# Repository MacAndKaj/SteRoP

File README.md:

# SteRoP
A project with STM32L476 Discovery

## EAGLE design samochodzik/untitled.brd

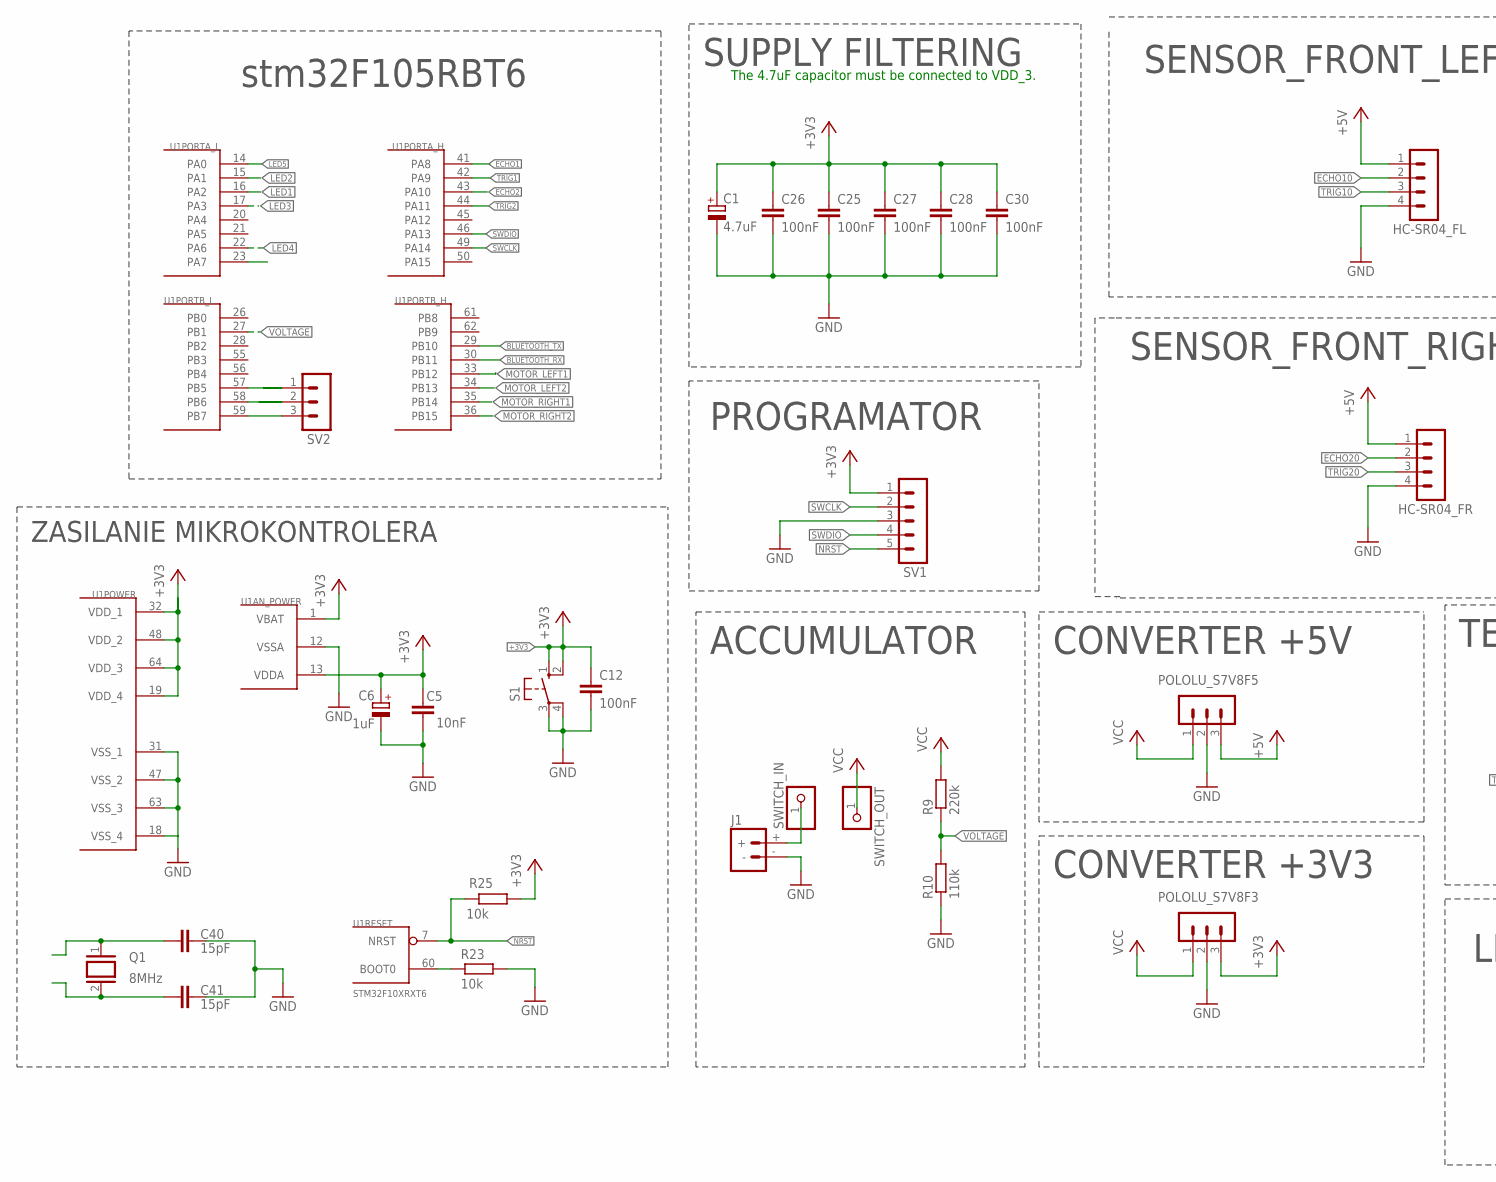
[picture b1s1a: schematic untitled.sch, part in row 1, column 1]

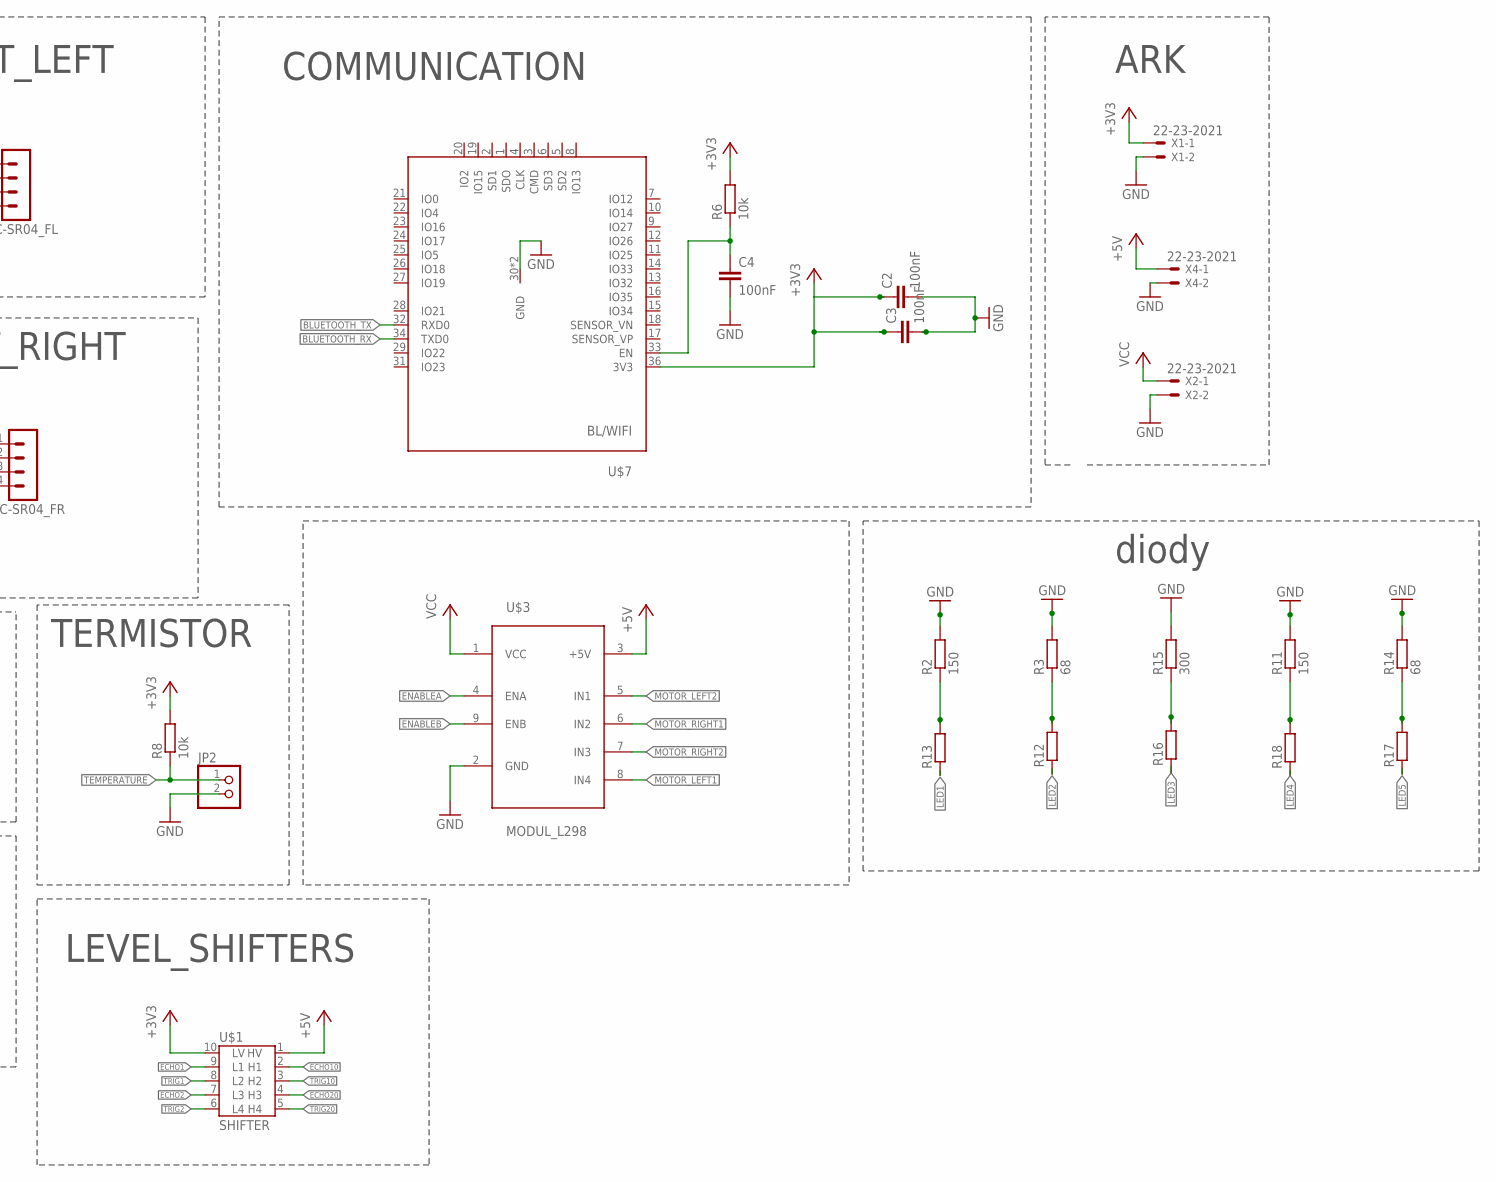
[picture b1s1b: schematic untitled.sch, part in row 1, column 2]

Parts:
C1: 4.7uF; A/3216-18R
C2, C3, C4, C12, C25, C26, C27, C28, C30: 100nF; C0805
C5: 10nF; C0805
C6: 1uF; B/3528-21W
C40, C41: 15pF; C0805
HC-SR04_FL, HC-SR04_FR: MA04-1
J1: BATTERY_CONN_DEANS; DEANS
JP2: PINHD-1X2; 1X02
POLOLU_S7V8F3, POLOLU_S7V8F5: MA03-1
Q1: 8MHz; Q
R2, R11: 150; R0805
R3, R14: 68; M0805
R6: 10k; M0805
R8, R23, R25: 10k; R0805
R9: 220k; R0805
R10: 110k; R0805
R12, R13, R16, R17, R18: R-EU_0204/5; 0204/5
R15: 300; R0805
S1: TACT_SWITCH; B3F-10XX
SV1: MA05-1
SV2: MA03-1
SWITCH_IN: PINHD-1X1; 1X01
SWITCH_OUT: PINHD-1X1; 1X01
U1: STM32F10XRXT6; TQFP64
U$1: SHIFTER
U$3: MODUL_L298
U$7: BL/WIFI
X1, X2, X4: 22-23-2021

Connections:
+3V3: C1.+, C2.1, C3.1, C5.2, C6.+, C12.1, C25.1, C26.1, C27.1, C28.1, C30.1, POLOLU_S7V8F3.3, R6.2, R8.2, R25.2, S1.1 (S), S1.2 (S1), SV1.1, U1.1 (VBAT), U1.13 (VDDA), U1.19 (VDD_4), U1.32 (VDD_1), U1.48 (VDD_2), U1.64 (VDD_3), U$1.10 (LV), U$7.36 (3V3), X1.1
+5V: HC-SR04_FL.1, HC-SR04_FR.1, POLOLU_S7V8F5.3, U$1.1 (HV), U$3.3 (+5V), X4.1
BLUETOOTH_RX: U1.30 (PB11), U$7.34 (TXD0)
BLUETOOTH_TX: U1.29 (PB10), U$7.32 (RXD0)
ECHO1: U1.41 (PA8), U$1.9 (L1)
ECHO2: U1.43 (PA10), U$1.7 (L3)
ECHO10: HC-SR04_FL.2, U$1.2 (H1)
ECHO20: HC-SR04_FR.2, U$1.4 (H3)
ENABLEA: U$3.4 (ENA)
ENABLEB: U$3.9 (ENB)
GND: C1.-, C2.2, C3.2, C4.2, C5.1, C6.-, C12.2, C25.2, C26.2, C27.2, C28.2, C30.2, C40.2, C41.2, HC-SR04_FL.4, HC-SR04_FR.4, J1.-, JP2.2, POLOLU_S7V8F3.2, POLOLU_S7V8F5.2, R2.2, R3.2, R10.1, R11.2, R14.2, R15.2, R23.1, S1.3, S1.4 (P1), SV1.3, U1.12 (VSSA), U1.18 (VSS_4), U1.31 (VSS_1), U1.47 (VSS_2), U1.63 (VSS_3), U$3.2 (GND), U$7.30 (GND), U$7.35 (GND), X1.2, X2.2, X4.2
LED1: R13.1, U1.16 (PA2)
LED2: R12.1, U1.15 (PA1)
LED3: R16.1, U1.17 (PA3)
LED4: R18.1, U1.22 (PA6)
LED5: R17.1, U1.14 (PA0)
MOTOR_LEFT1: U1.33 (PB12), U$3.8 (IN4)
MOTOR_LEFT2: U1.34 (PB13), U$3.5 (IN1)
MOTOR_RIGHT1: U1.35 (PB14), U$3.6 (IN2)
MOTOR_RIGHT2: U1.36 (PB15), U$3.7 (IN3)
unnamed: SV2.3, U1.59 (PB7)
unnamed: R23.2, U1.60 (BOOT0)
unnamed: C40.1, Q1.1
unnamed: C41.1, Q1.2
unnamed: SV2.2, U1.58 (PB6)
unnamed: J1.+, SWITCH_IN.1
unnamed: SV2.1, U1.57 (PB5)
unnamed: C4.1, R6.1, U$7.33 (EN)
unnamed: R2.1, R13.2
unnamed: R3.1, R12.2
unnamed: R11.1, R18.2
unnamed: R14.1, R17.2
unnamed: R15.1, R16.2
NRST: R25.1, SV1.5, U1.7 (NRST)
SWCLK: SV1.2, U1.49 (PA14)
SWDIO: SV1.4, U1.46 (PA13)
TEMPERATURE: JP2.1, R8.1
TRIG1: U1.42 (PA9), U$1.8 (L2)
TRIG2: U1.44 (PA11), U$1.6 (L4)
TRIG10: HC-SR04_FL.3, U$1.3 (H2)
TRIG20: HC-SR04_FR.3, U$1.5 (H4)
VCC: POLOLU_S7V8F3.1, POLOLU_S7V8F5.1, R9.2, SWITCH_OUT.1, U$3.1 (VCC), X2.1
VOLTAGE: R9.1, R10.2, U1.27 (PB1)

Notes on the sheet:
SUPPLY FILTERING
The 4.7uF capacitor must be connected to VDD_3.
PROGRAMATOR
ACCUMULATOR
CONVERTER +5V
CONVERTER +3V3
SENSOR_FRONT_RIGHT
SENSOR_FRONT_LEFT
TERMISTOR
LEVEL_SHIFTERS
COMMUNICATION
ZASILANIE MIKROKONTROLERA
diody
ARK
stm32F105RBT6

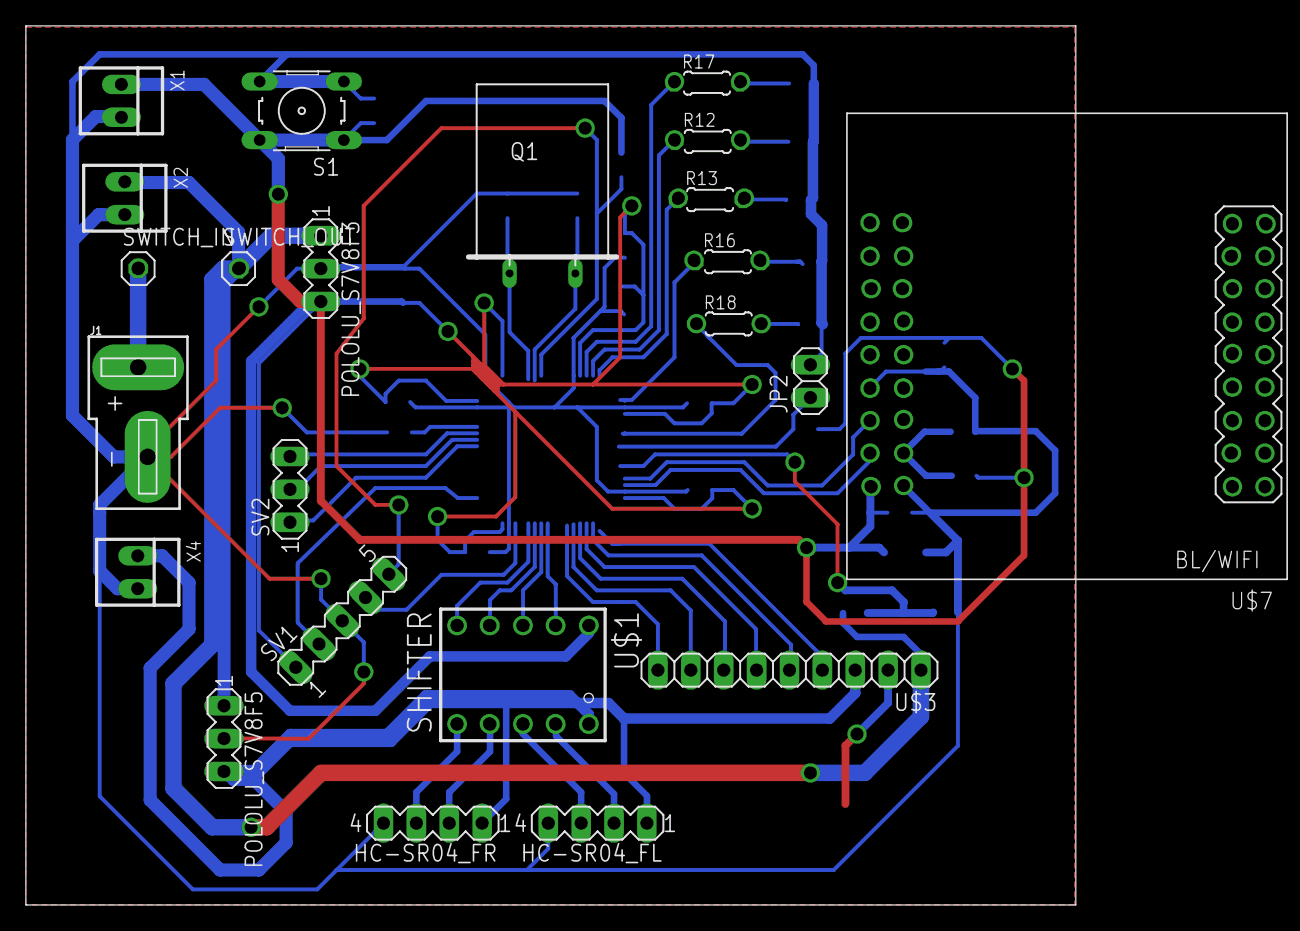
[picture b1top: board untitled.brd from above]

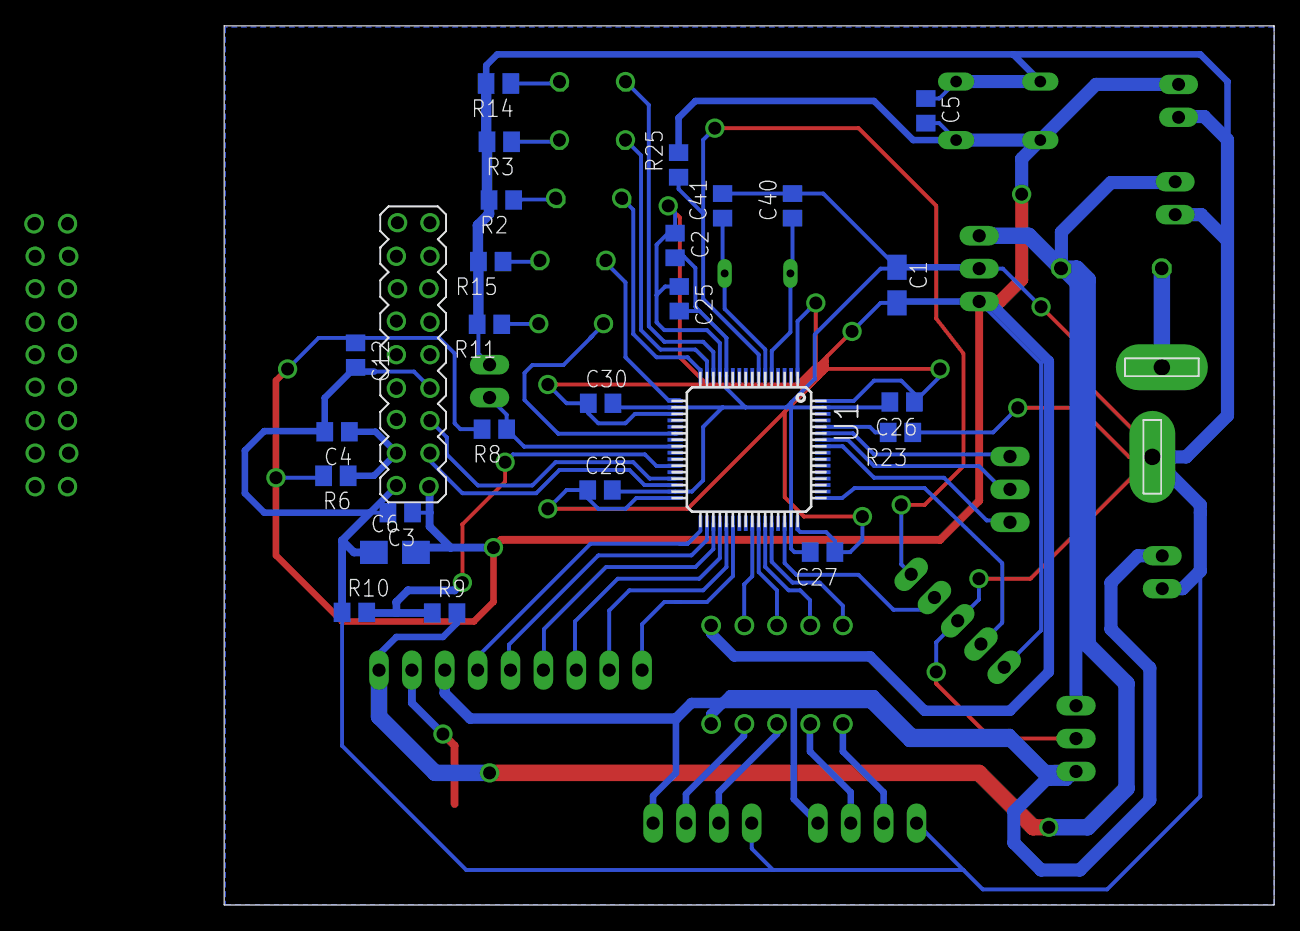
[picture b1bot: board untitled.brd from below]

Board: 2 copper layers, 81.1 x 67.9 mm, 49 parts (26 on the bottom side), 41 nets.

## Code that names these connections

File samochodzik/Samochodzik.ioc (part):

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Mcu.Name=STM32F105R(8-B-C)Tx
Mcu.Package=LQFP64
Mcu.UserName=STM32F105RBTx
PA0-WKUP.GPIOParameters=GPIO_Label
PA0-WKUP.GPIO_Label=led5
PA0-WKUP.Signal=GPIO_Output
PA1.GPIOParameters=GPIO_Label
PA1.GPIO_Label=led4
PA1.Signal=GPIO_Output
PA10.GPIOParameters=GPIO_Label
PA10.GPIO_Label=echo_right
PA10.Signal=S_TIM1_CH3
PA11.GPIOParameters=GPIO_Label
PA11.GPIO_Label=trig_right
PA11.Signal=S_TIM1_CH4
PA13.Mode=Serial_Wire
PA13.Signal=SYS_JTMS-SWDIO
PA14.Mode=Serial_Wire
PA14.Signal=SYS_JTCK-SWCLK
PA2.GPIOParameters=GPIO_Label
PA2.GPIO_Label=led3
PA2.Signal=GPIO_Output
PA3.GPIOParameters=GPIO_Label
PA3.GPIO_Label=led2
PA3.Signal=GPIO_Output
PA6.GPIOParameters=GPIO_Label
PA6.GPIO_Label=led1
PA6.Signal=GPIO_Output
PA8.GPIOParameters=GPIO_Label
PA8.GPIO_Label=echo_left
PA8.Signal=S_TIM1_CH1
PA9.GPIOParameters=GPIO_Label
PA9.GPIO_Label=trig_left
PA9.Signal=S_TIM1_CH2
PB1.GPIOParameters=GPIO_Label
PB1.GPIO_Label=battery_voltage
PB1.Signal=ADCx_IN9
PB10.GPIOParameters=GPIO_Label
PB10.GPIO_Label=bluetooth_tx
PB10.Mode=Asynchronous
PB10.Signal=USART3_TX
PB11.GPIOParameters=GPIO_Label
PB11.GPIO_Label=bluetooth_rx
PB11.Mode=Asynchronous
PB11.Signal=USART3_RX
PB12.Signal=GPIO_Output
PB13.Signal=GPIO_Output
PB14.Signal=GPIO_Output
PB15.Signal=GPIO_Output
PC4.GPIOParameters=GPIO_Label
PC4.GPIO_Label=battery_temperature
PC4.Signal=ADCx_IN14
PC6.Signal=GPIO_Output
PD0-OSC_IN.Mode=HSE-External-Oscillator
PD0-OSC_IN.Signal=RCC_OSC_IN
PD1-OSC_OUT.Mode=HSE-External-Oscillator
PD1-OSC_OUT.Signal=RCC_OSC_OUT
RCC.SYSCLKFreq_VALUE=32000000
RCC.SYSCLKSource=RCC_SYSCLKSOURCE_PLLCLK

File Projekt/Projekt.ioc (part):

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Mcu.Name=STM32L476V(C-E-G)Tx
Mcu.Package=LQFP100
Mcu.UserName=STM32L476VGTx
PA0.GPIOParameters=GPIO_Label
PA0.GPIO_Label=JOY_CENTER
PA0.Signal=GPXTI0
PB2.GPIOParameters=GPIO_Label
PB2.GPIO_Label=LD_R
PB2.Signal=GPIO_Output
PB6.GPIOParameters=GPIO_Label
PB6.GPIO_Label=BLUETOOTH_TX
PB6.Mode=Asynchronous
PB6.Signal=USART1_TX
PB7.GPIOParameters=GPIO_Label
PB7.GPIO_Label=BLUETOOTH_RX
PB7.Mode=Asynchronous
PB7.Signal=USART1_RX
PC0.GPIOParameters=GPIO_Label
PC0.GPIO_Label=MAG_CS
PC0.Signal=GPIO_Output
PC14-OSC32_IN\ (PC14).Mode=LSE-External-Oscillator
PC14-OSC32_IN\ (PC14).Signal=RCC_OSC32_IN
PC15-OSC32_OUT\ (PC15).Mode=LSE-External-Oscillator
PC15-OSC32_OUT\ (PC15).Signal=RCC_OSC32_OUT
PD1.GPIOParameters=GPIO_PuPd,GPIO_Label
PD1.GPIO_Label=ACC_SCK
PD1.GPIO_PuPd=GPIO_NOPULL
PD1.Mode=Simplex_Bidirectional_Master
PD1.Signal=SPI2_SCK
PD4.GPIOParameters=GPIO_PuPd,GPIO_Label
PD4.GPIO_Label=ACC_MOSI
PD4.GPIO_PuPd=GPIO_NOPULL
PD4.Mode=Simplex_Bidirectional_Master
PD4.Signal=SPI2_MOSI
PD5.Mode=Asynchronous
PD5.Signal=USART2_TX
PD6.Mode=Asynchronous
PD6.Signal=USART2_RX
PE0.GPIOParameters=GPIO_Label
PE0.GPIO_Label=ACC_CS
PE0.Signal=GPIO_Output
PE8.GPIOParameters=GPIO_Label
PE8.GPIO_Label=LD_G
PE8.Signal=GPIO_Output
PH0-OSC_IN\ (PH0).Mode=HSE-External-Oscillator
PH0-OSC_IN\ (PH0).Signal=RCC_OSC_IN
PH1-OSC_OUT\ (PH1).Mode=HSE-External-Oscillator
PH1-OSC_OUT\ (PH1).Signal=RCC_OSC_OUT
RCC.HSE_VALUE=8000000
RCC.SYSCLKFreq_VALUE=80000000
RCC.SYSCLKSource=RCC_SYSCLKSOURCE_PLLCLK
board=32L476GDISCOVERY
boardIOC=true

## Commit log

2018-04-23 init
2018-04-23 Cube
2018-04-29 zmiana
2018-05-14 projekt
2018-05-14 porzadki
2018-05-14 Patryjc
2018-05-14 cube samochodzik
2018-05-14 Patryjcusz zadanie
2018-05-15 nowosci
2018-05-15 raport
2018-05-23 akcelerometr dziala, katy Roll i Pitch poprawne
2018-06-05 silniki dzialaja, jezdzi
2018-06-09 komunikacja dziala, samochodzik jezdzi, akcelerometr dziala, czujniki dzialaja, trzeba konczyc
2018-06-09 jezdzdi zdalnie sterowany
2018-06-10 dziala, chcialbym wiecej ale dziala

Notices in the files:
parts and their libraries:
SparkFun-Connectors: Licensing: Creative Commons ShareAlike 4.0 International - https://creativecommons.org/licenses/by-sa/4.0
